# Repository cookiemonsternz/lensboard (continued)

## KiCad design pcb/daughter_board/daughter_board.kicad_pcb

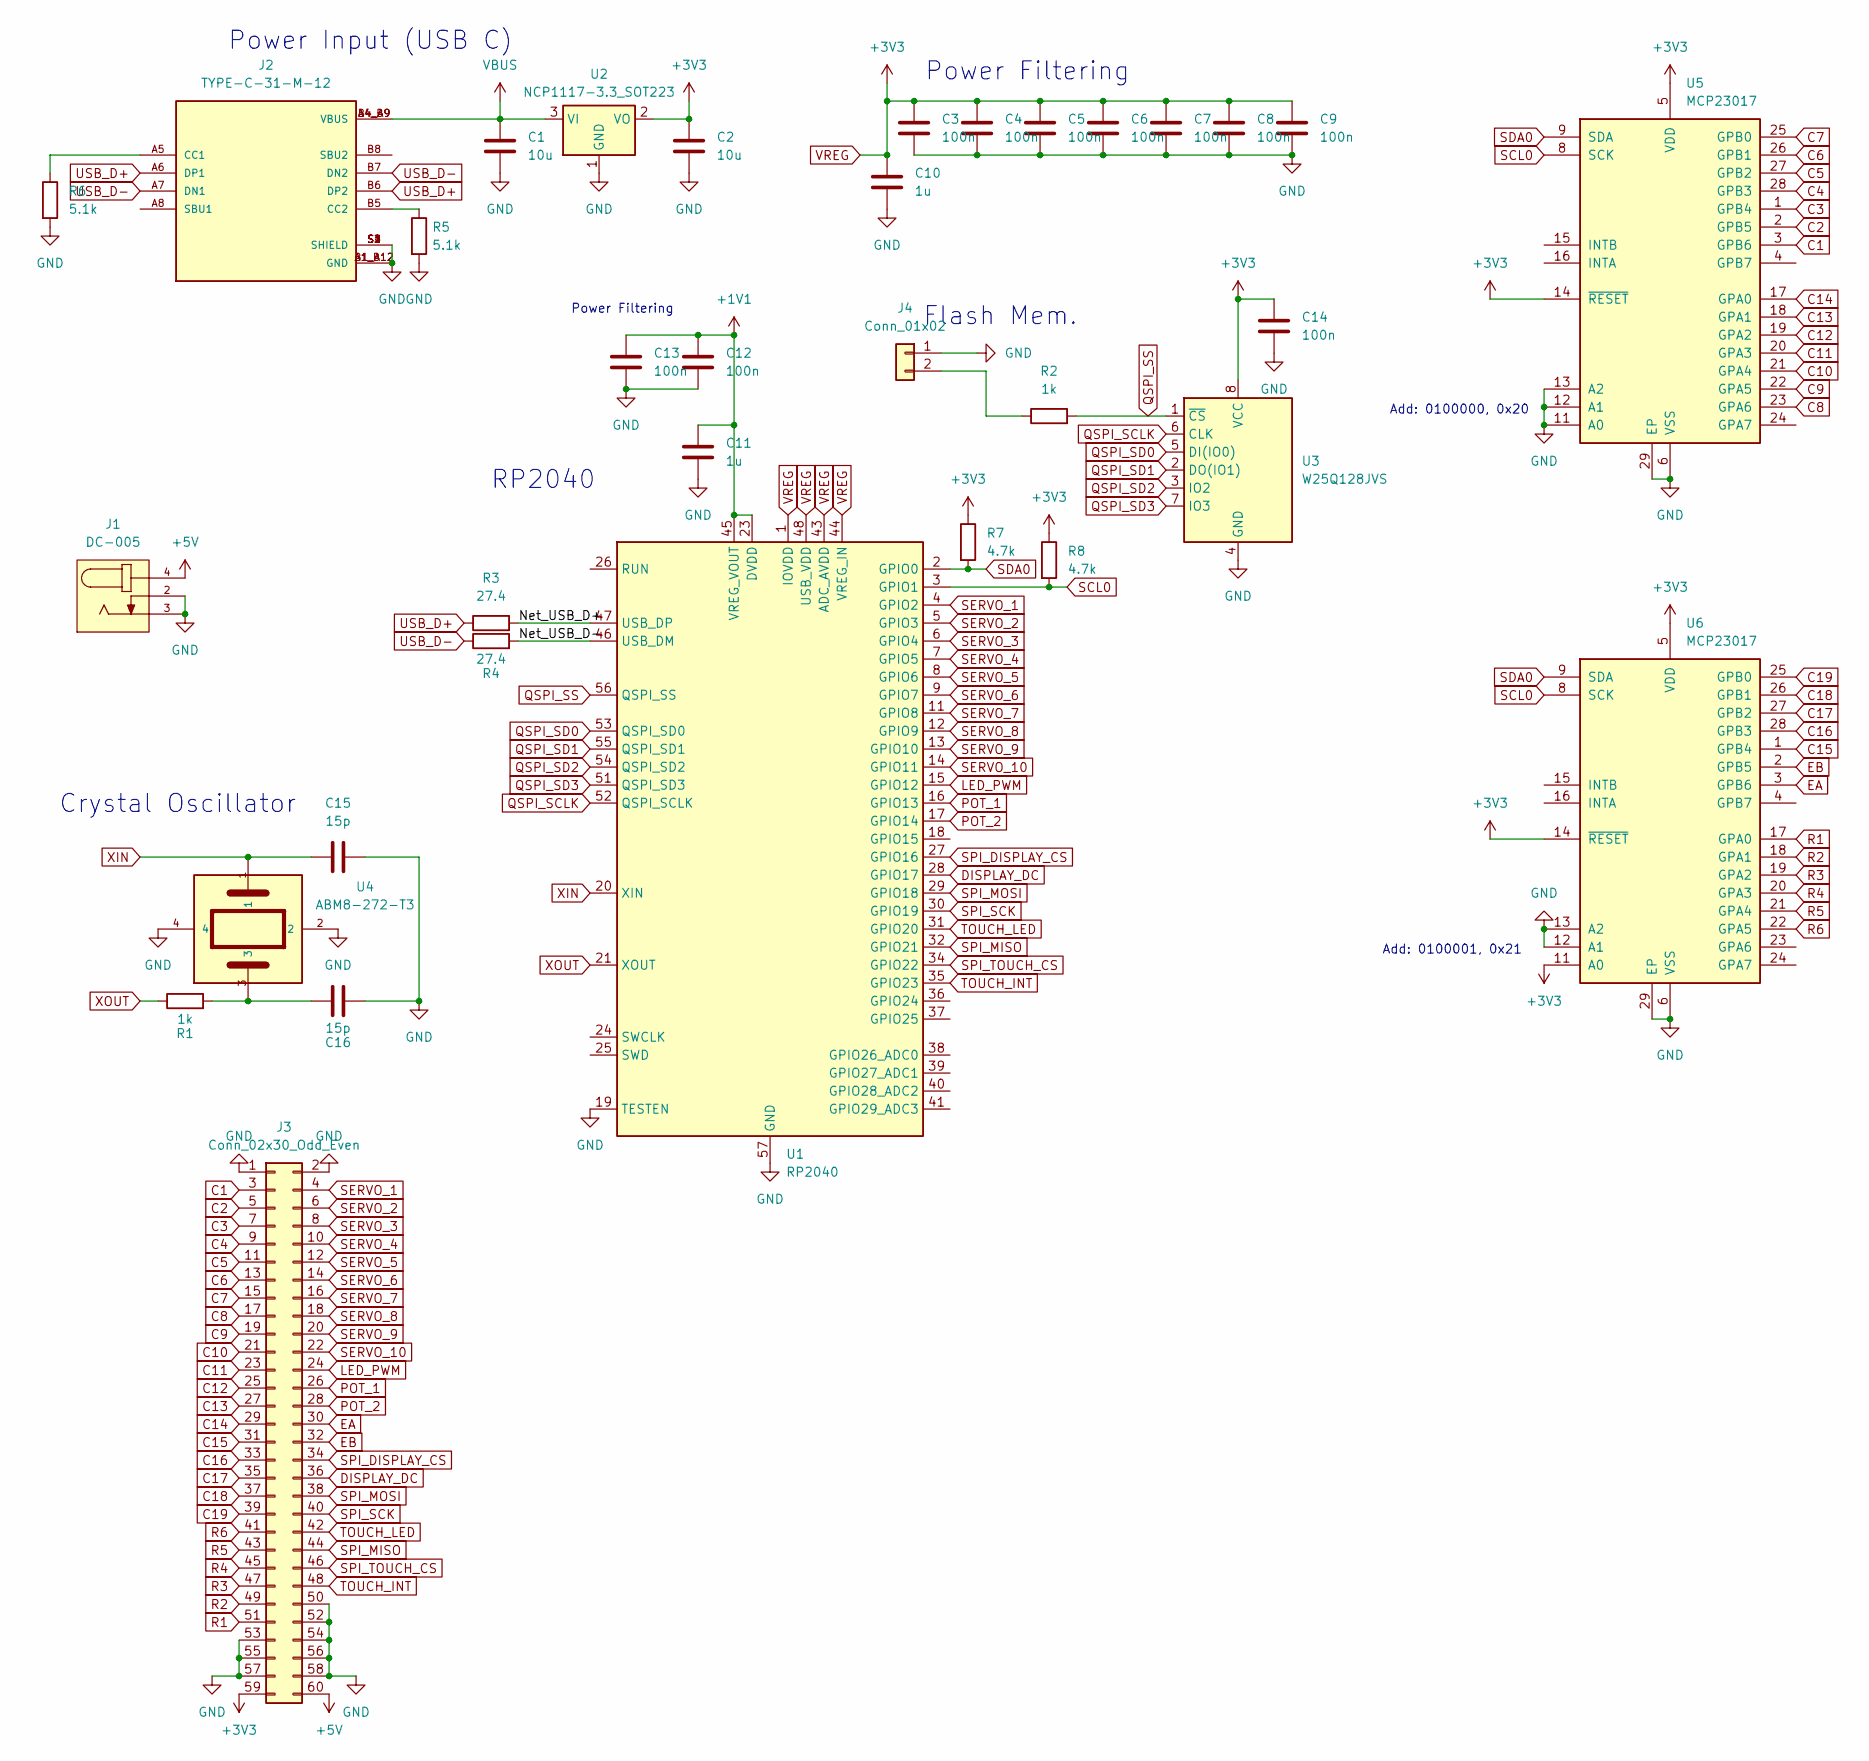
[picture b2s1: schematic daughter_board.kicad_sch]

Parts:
C1, C2: 10u; C_0603_1608Metric
C3, C4, C5, C6, C7, C8, C9, C12, C13, C14: 100n; C_0402_1005Metric
C10, C11: 1u; C_0603_1608Metric
C15, C16: 15p; C_0402_1005Metric
J1: DC-005; NINIGI_DC-005
J2: TYPE-C-31-M-12; HRO_TYPE-C-31-M-12; PARTREV 2020.12.08
J3: Conn_02x30_Odd_Even; PinHeader_2x30_P1.27mm_Vertical
J4: Conn_01x02; PinHeader_1x02_P1.27mm_Vertical
R1, R2: 1k; R_0402_1005Metric
R3, R4: 27.4; R_0402_1005Metric
R5, R6: 5.1k; R_0402_1005Metric
R7, R8: 4.7k; R_0402_1005Metric
U1: RP2040; QFN-56-1EP_7x7mm_P0.4mm_EP3.2x3.2mm
U2: NCP1117-3.3_SOT223; SOT-223-3_TabPin2
U3: W25Q128JVS; SOIC127P790X216-8N
U4: ABM8-272-T3; XTAL_ABM8-272-T3
U5, U6: MCP23017; QFN-28-1EP_6x6mm_P0.65mm_EP4.25x4.25mm

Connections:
+1V1: C11.2, C12.1, C13.1, U1.23 (DVDD), U1.45 (VREG_VOUT), U1.50 (DVDD)
+5V: J1.4, J3.60
/Net_USB_D+: R3.2, U1.47 (USB_DP)
/Net_USB_D-: R4.2, U1.46 (USB_DM)
C1: J3.3, U5.3 (GPB6)
C2: J3.5, U5.2 (GPB5)
C3: J3.7, U5.1 (GPB4)
C4: J3.9, U5.28 (GPB3)
C5: J3.11, U5.27 (GPB2)
C6: J3.13, U5.26 (GPB1)
C7: J3.15, U5.25 (GPB0)
C8: J3.17, U5.23 (GPA6)
C9: J3.19, U5.22 (GPA5)
C10: J3.21, U5.21 (GPA4)
C11: J3.23, U5.20 (GPA3)
C12: J3.25, U5.19 (GPA2)
C13: J3.27, U5.18 (GPA1)
C14: J3.29, U5.17 (GPA0)
C15: J3.31, U6.1 (GPB4)
C16: J3.33, U6.28 (GPB3)
C17: J3.35, U6.27 (GPB2)
C18: J3.37, U6.26 (GPB1)
C19: J3.39, U6.25 (GPB0)
DISPLAY_DC: J3.36, U1.28 (GPIO17)
EA: J3.30, U6.3 (GPB6)
EB: J3.32, U6.2 (GPB5)
GND: C1.2, C2.2, C3.2, C4.2, C5.2, C6.2, C7.2, C8.2, C9.2, C10.2, C11.1, C12.2, C13.2, C14.2, C15.2, C16.1, J1.2, J1.3, J2.A1_B12 (GND), J2.B1_A12 (GND), J2.S1 (SHIELD), J2.S2 (SHIELD), J2.S3 (SHIELD), J2.S4 (SHIELD), J3.1, J3.2, J3.50, J3.52, J3.53, J3.54, J3.55, J3.56, J3.57, J3.58, J4.1, R5.2, R6.2, U1.19 (TESTEN), U1.57 (GND), U2.1 (GND), U3.4 (GND), U4.2, U4.4, U5.6 (VSS), U5.11 (A0), U5.12 (A1), U5.13 (A2), U5.29 (EP), U6.6 (VSS), U6.12 (A1), U6.13 (A2), U6.29 (EP)
LED_PWM: J3.24, U1.15 (GPIO12)
unnamed: C16.2, R1.2, U4.3
unnamed: J2.A5 (CC1), R6.1
unnamed: J2.B5 (CC2), R5.1
unnamed: J4.2, R2.1
POT_1: J3.26, U1.16 (GPIO13)
POT_2: J3.28, U1.17 (GPIO14)
QSPI_SCLK: U1.52 (QSPI_SCLK), U3.6 (CLK)
QSPI_SD0: U1.53 (QSPI_SD0), U3.5 (DI(IO0))
QSPI_SD1: U1.55 (QSPI_SD1), U3.2 (DO(IO1))
QSPI_SD2: U1.54 (QSPI_SD2), U3.3 (IO2)
QSPI_SD3: U1.51 (QSPI_SD3), U3.7 (IO3)
QSPI_SS: R2.2, U1.56 (QSPI_SS), U3.1 (~CS)
R1: J3.51, U6.17 (GPA0)
R2: J3.49, U6.18 (GPA1)
R3: J3.47, U6.19 (GPA2)
R4: J3.45, U6.20 (GPA3)
R5: J3.43, U6.21 (GPA4)
R6: J3.41, U6.22 (GPA5)
SCL0: R8.2, U1.3 (GPIO1), U5.8 (SCK), U6.8 (SCK)
SDA0: R7.2, U1.2 (GPIO0), U5.9 (SDA), U6.9 (SDA)
SERVO_1: J3.4, U1.4 (GPIO2)
SERVO_2: J3.6, U1.5 (GPIO3)
SERVO_3: J3.8, U1.6 (GPIO4)
SERVO_4: J3.10, U1.7 (GPIO5)
SERVO_5: J3.12, U1.8 (GPIO6)
SERVO_6: J3.14, U1.9 (GPIO7)
SERVO_7: J3.16, U1.11 (GPIO8)
SERVO_8: J3.18, U1.12 (GPIO9)
SERVO_9: J3.20, U1.13 (GPIO10)
SERVO_10: J3.22, U1.14 (GPIO11)
SPI_DISPLAY_CS: J3.34, U1.27 (GPIO16)
SPI_MISO: J3.44, U1.32 (GPIO21)
SPI_MOSI: J3.38, U1.29 (GPIO18)
SPI_SCK: J3.40, U1.30 (GPIO19)
SPI_TOUCH_CS: J3.46, U1.34 (GPIO22)
TOUCH_INT: J3.48, U1.35 (GPIO23)
TOUCH_LED: J3.42, U1.31 (GPIO20)
USB_D+: J2.A6 (DP1), J2.B6 (DP2), R3.1
USB_D-: J2.A7 (DN1), J2.B7 (DN2), R4.1
VBUS: C1.1, J2.A4_B9 (VBUS), J2.B4_A9 (VBUS), U2.3 (VI)
VREG: C2.1, C3.1, C4.1, C5.1, C6.1, C7.1, C8.1, C9.1, C10.1, C14.1, J3.59, R7.1, R8.1, U1.1 (IOVDD), U1.10 (IOVDD), U1.22 (IOVDD), U1.33 (IOVDD), U1.42 (IOVDD), U1.43 (ADC_AVDD), U1.44 (VREG_IN), U1.48 (USB_VDD), U1.49 (IOVDD), U2.2 (VO), U3.8 (VCC), U5.5 (VDD), U5.14 (~RESET), U6.5 (VDD), U6.11 (A0), U6.14 (~RESET)
XIN: C15.1, U1.20 (XIN), U4.1
XOUT: R1.1, U1.21 (XOUT)

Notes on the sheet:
RP2040
Add: 0100000, 0x20
Crystal Oscillator
Flash Mem.
Power Filtering
Power Filtering
Add: 0100001, 0x21
Power Input (USB C)

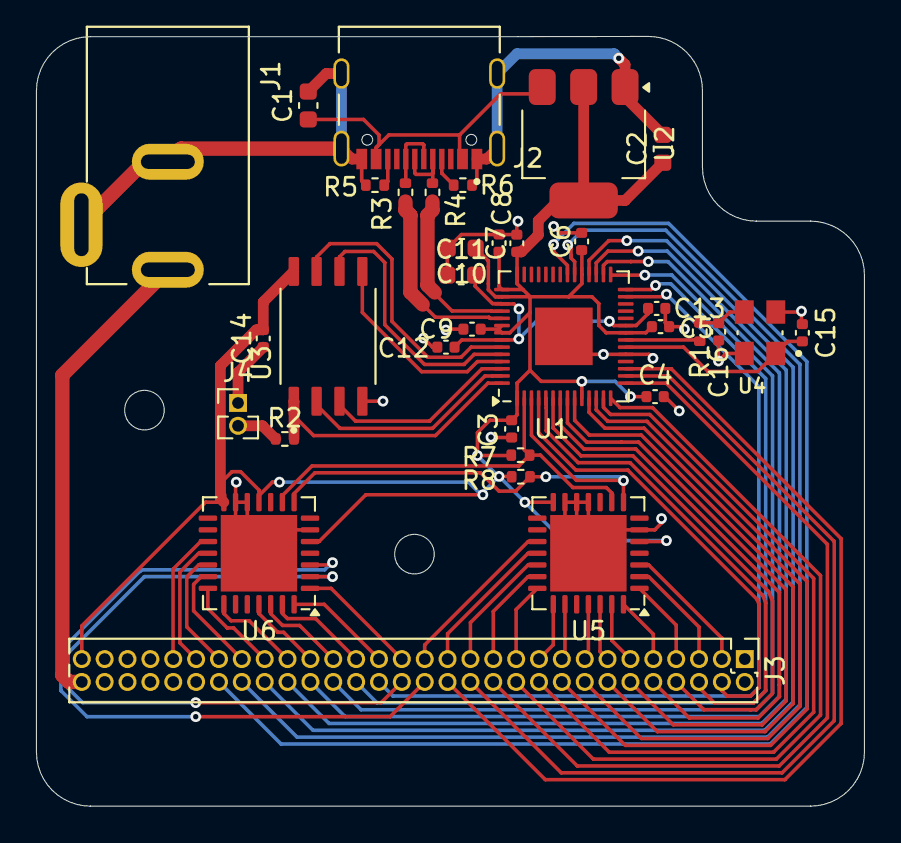
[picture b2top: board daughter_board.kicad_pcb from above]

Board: 2 copper layers, 46.0 x 42.8 mm, 34 parts (0 on the bottom side), 71 nets.

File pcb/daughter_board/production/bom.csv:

Designator,Footprint,Quantity,Value,LCSC Part #
"C1, C2",0603,2,10u,
"C10, C11",0603,2,1u,
"C12, C13, C14, C3, C4, C5, C6, C7, C8, C9",0402,10,100n,
"C15, C16",0402,2,15p,
J1,NINIGI_DC-005,1,DC-005,
J2,HRO_TYPE-C-31-M-12,1,TYPE-C-31-M-12,
J3,PinHeader_2x30_P1.27mm_Vertical,1,Conn_02x30_Odd_Even,
J4,PinHeader_1x02_P1.27mm_Vertical,1,Conn_01x02,
"R1, R2",0402,2,1k,
"R3, R4",0402,2,27.4,
"R5, R6",0402,2,5.1k,
"R7, R8",0402,2,4.7k,
U1,QFN-56-1EP_7x7mm_P0.4mm_EP3.2x3.2mm,1,RP2040,
U2,SOT-223-3_TabPin2,1,NCP1117-3.3_SOT223,
U3,SOIC127P790X216-8N,1,W25Q128JVS,
U4,XTAL_ABM8-272-T3,1,ABM8-272-T3,
"U5, U6",QFN-28-1EP_6x6mm_P0.65mm_EP4.25x4.25mm,2,MCP23017,

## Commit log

2025-05-15 test img
2025-05-15 Add to journal more
2025-05-15 resize images
2025-05-15 change headings
2025-05-15 add symlink to journal
2025-05-15 add actual symlink
2025-05-15 revert changes to journal
2025-05-15 add images to symlink directory
2025-05-17 add journal entry 2
2025-05-17 fix md
2025-05-21 key matrix schematicised
2025-05-22 move images and finish schematic
2025-05-22 move image links to github hosted
2025-05-27 keyb pcb finished w/ wrong switches
2025-06-11 yeah, just everything
2025-06-11 u[date to github links for images
2025-06-11 reroute power and usb :skull:
2025-06-13 more touch ups
2025-06-13 add render images
2025-06-13 restructure project
2025-06-13 add touchscreen to bom
2025-06-13 Remove csv from gitignore
2025-06-13 rename boms
2025-06-13 add final journal entry + sum times
2025-06-14 final bom update + prod files
2025-06-14 add first iteration firmware
2025-06-19 Commit before pcb refactor
2025-06-21 finish pcb refactor
2025-06-24 add renders and finish and export case
2025-06-24 add stl
2025-06-24 fix stl
